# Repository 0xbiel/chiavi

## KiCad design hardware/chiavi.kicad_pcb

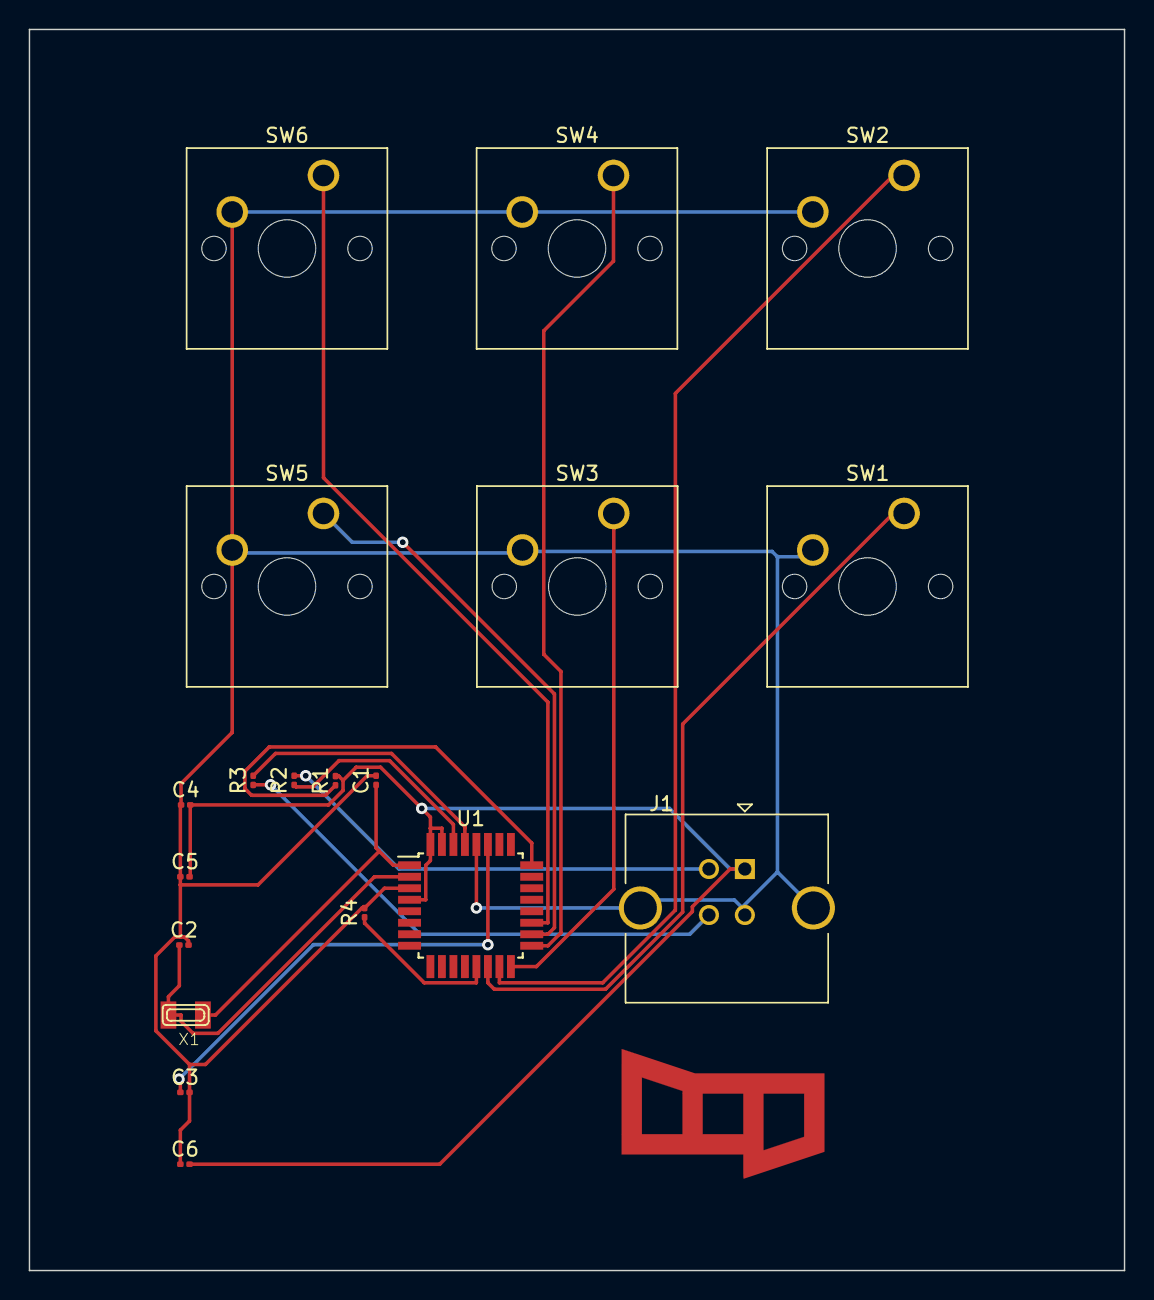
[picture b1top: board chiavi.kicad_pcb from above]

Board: 2 copper layers, 76.2 x 86.4 mm, 19 parts (0 on the bottom side), 17 nets.

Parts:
C1, C2, C3, C4, C5, C6: C; C_0201_0603Metric
J1: USB_B; USB_B_TE_5787834_Vertical
R1, R2, R3, R4: R; R_0201_0603Metric
SW1, SW2, SW3, SW4, SW5, SW6: SW_SPST; SW_Cherry_MX_1.00u_PCB
U1: ATmega32U2-AU; TQFP-32_7x7mm_P0.8mm
X1: XTAL; XTAL3215

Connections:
GND: C1.2, C2.2, C3.2, C4.1, C5.1, C6.1, J1.4, J1.5, R4.2, SW1.2, SW2.2, SW3.2, SW4.2, SW5.2, SW6.2, U1.3, U1.28
unnamed: C1.1, U1.1, X1.P$1
unnamed: C2.1, U1.2, X1.P$2
unnamed: C3.1, U1.27
unnamed: J1.2, R2.2
unnamed: J1.3, R3.1
unnamed: R1.1, U1.24
unnamed: R2.1, U1.30
unnamed: R3.2, U1.29
unnamed: R4.1, U1.13
unnamed: SW1.1, U1.14
unnamed: SW2.1, U1.15
unnamed: SW3.1, U1.16
unnamed: SW4.1, U1.17
unnamed: SW5.1, U1.18
unnamed: SW6.1, U1.19
VCC: C4.2, C5.2, C6.2, J1.1, R1.2, U1.4, U1.31, U1.32

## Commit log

2020-05-13 add firmware
2020-06-28 rename everything
2020-07-03 update logo material
